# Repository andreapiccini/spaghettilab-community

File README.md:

<p align="center">
  <a href="https://spaghetti-lab.my.canva.site/">Website</a> •
  <a href="https://spaghetti-lab.my.canva.site/join-newsletter">Newsletter</a>
</p>

# SpaghettiLAB Community

From prototype to product.

SpaghettiLAB Community is the open development platform for learning,
experimenting, and building modular embedded and IoT prototypes. It includes
reference hardware, firmware, local software, protocols, integrations, tests,
and examples without artificial feature restrictions.

A prototype is not automatically suitable for production. Professional
deployments also require qualified hardware, secure provisioning, verified
updates, release traceability, lifecycle maintenance, and accountable support.
Those production capabilities are developed and delivered separately so that
organizations can adopt SpaghettiLAB without weakening the open Community
platform.

## Repository structure

- `hardware/` — Core, Backbone, and Module reference designs.
- `firmware/` — Community firmware, SDKs, examples, and verification.
- `software/` — Local Studio, dashboard, Node-RED integration, and packages.
- `contracts/` — Public, language-neutral protocol contracts and golden fixtures.
- `examples/` — End-to-end example systems.
- `docs/` — Documentation licensing and notices.

The Community hardware tree intentionally contains editable KiCad sources, not
generated manufacturing packages. Official production files, factory tooling,
secure provisioning infrastructure, managed cloud services, and commercial
support are maintained separately.

## Open-core model

SpaghettiLAB follows an open-core hardware model with a clear boundary:

- **Community layer:** the source files actually published in this repository,
  licensed under the open-source and open-hardware licences listed below. These
  licences permit commercial use when their conditions are followed.
- **Production layer:** the separately maintained, release-specific package used
  for official commercial products and authorized manufacturing partners.

The Production layer is not part of this repository. It may include validated
Gerber and drill outputs, approved BOM and alternate-part data, pick-and-place
files, panelization and assembly profiles, test fixtures and procedures,
production firmware or provisioning material, enclosure and packaging files,
quality-control criteria, release traceability, and supplier-specific data.
Access to those materials, use of official SpaghettiLAB branding, and the right
to present a product as official or partner-produced require prior written
authorization under a separate commercial or manufacturing agreement.

Anyone may generate their own manufacturing outputs from the public hardware
sources and make or sell products as permitted by CERN-OHL-S-2.0. Such products
must comply with that licence and must not imply official manufacture,
certification, warranty, endorsement, or partnership. See
[`COMMERCIAL.md`](COMMERCIAL.md) and [`TRADEMARK.md`](TRADEMARK.md).

## Hardware projects

- `hardware/core/core.kicad_pro`
- `hardware/backbone/backbone.kicad_pro`
- `hardware/modules/nfc-tag/nfc-tag.kicad_pro`

The KiCad source files embed the symbols and footprints already used by each
design. Some optional 3D models reference the `SPAGHETTI_LIB` environment
variable and are not required to open the schematic or PCB.

## Community and production

The Community platform is intended for education, research, development,
prototyping, and open products. Organizations may evaluate and extend it under
the applicable open-source and open-hardware licenses.

SpaghettiLAB Production adds the controlled engineering work needed to turn a
prototype into a supported product: qualified hardware, secure device identity,
signed releases, manufacturing support, managed updates, fleet operations, and
long-term maintenance.

## Citation

If you use SpaghettiLAB in research, publications, articles, videos, educational
material, or derivative projects, please cite:

> Piccini, A. (2026).  
> SpaghettiLAB: Modular Stackable Electronics Platform.  
> GitHub Repository.  
> https://github.com/andreapiccini/SpaghettiLAB

A machine-readable citation file is available in `CITATION.cff`.

## Licensing

The current Community generation retains the licenses already applied to its
components:

| Content | License |
|---|---|
| Firmware | GPL-3.0-or-later |
| Public applications and services | AGPL-3.0-or-later |
| Protocols and selected integration SDKs | Apache License 2.0 |
| Hardware reference designs | CERN-OHL-S-2.0 |
| Documentation | CC BY 4.0 |

See [`LICENSES.md`](LICENSES.md) for the exact repository map,
[`CONTRIBUTING.md`](CONTRIBUTING.md) for DCO contribution requirements, and
[`TRADEMARK.md`](TRADEMARK.md) for product identity rules. The copyleft transition
does not alter rights granted for earlier versions.

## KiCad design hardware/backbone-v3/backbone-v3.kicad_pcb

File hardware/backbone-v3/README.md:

# Backbone V3

Aprire `backbone-v3.kicad_pro` in KiCad. Il progetto contiene lo schema gerarchico e il PCB da **68,5 × 63,5 mm**. L’[anteprima interattiva](anteprima-interattiva.html) simula i quattro comandi, Play/Stop, il blocco e le quattro memorie. Le modalità delle righe sono 3.3V, GND, MCU e X (scollegata). I tasti in basso hanno solo le icone.

## Touch

Un Holtek BS8112A-3 (LCSC C91296), alimentato a 3,3 V con C944 da 100 nF, legge i quattro elettrodi anulari sotto la solder mask. Usa il bus I²C interno esistente, con indirizzo a 7 bit `0x50`. L’ESP32-S3 e l’ESP32-S31 condividono la stessa interfaccia. Gli ingressi inutilizzati e KEY12/IRQ restano aperti.

| Ingresso | Bit di KeyStatus0 | Comando |
| --- | --- | --- |
| KEY1 | 0 | Play/Stop |
| KEY2 | 1 | + |
| KEY3 | 2 | Mode |
| KEY4 | 3 | Load/Save |

Il firmware deve leggere `KeyStatus0` (`0x08`) in polling, interpretando 1 come tasto premuto. L’I²C va configurato a non più di 100 kbit/s con supporto al clock stretching e timeout. Le soglie dei quattro canali si impostano in software all’avvio entro la finestra indicata nel datasheet. Il comportamento dei comandi è simulato nell’anteprima. I tre segmenti della batteria sono indipendenti e attendono il dato di carica dal modulo batteria.

## Frontale e LED

Il driver IS31FL3731 (I²C interno, 0x74) pilota 105 LED. La [mappa del frontale](layout.json) riporta le reti di anodo e catodo, il registro PWM e il codice LCSC per ciascun emettitore. Le 16 righe hanno 64 LED 0402 a ±45°. I 0603 sono stati usati dove le piazzole rispettano le aperture e lo spazio disponibile. In totale ci sono 86 LED 0402 e 19 LED 0603. Il logo usa 20 LED blu (16 da 0402 e 4 da 0603) distribuiti su simbolo e lettere.

Le finestre sono aperture nelle due solder mask con esclusione di rame sui quattro strati. Rimane FR-4 pieno. I LED sono componenti a emissione frontale, piazzati sul Top per la prova di montaggio rivolto verso il laminato. Servono un campione per verificare saldabilità, uniformità della luce e sensibilità degli elettrodi, e il routing del PCB prima della fabbricazione. J32 e J33 sono stati riposizionati per liberare le finestre.

## Verifica KiCad

Lo schema ha superato l’ERC senza errori. Sono state confrontate 1.049 associazioni piazzola–rete tra schema e PCB. Il DRC non segnala cortocircuiti o piazzole nelle aree ottiche. Restano 499 connessioni da instradare e segnalazioni su courtyard, serigrafia e distanze del PCB, comprese quelle dei contatti magnetici al bordo.

## Variante RGB

L’[anteprima RGB con MODE](anteprima-rgb-mode.html) conserva il confronto con la proposta precedente.

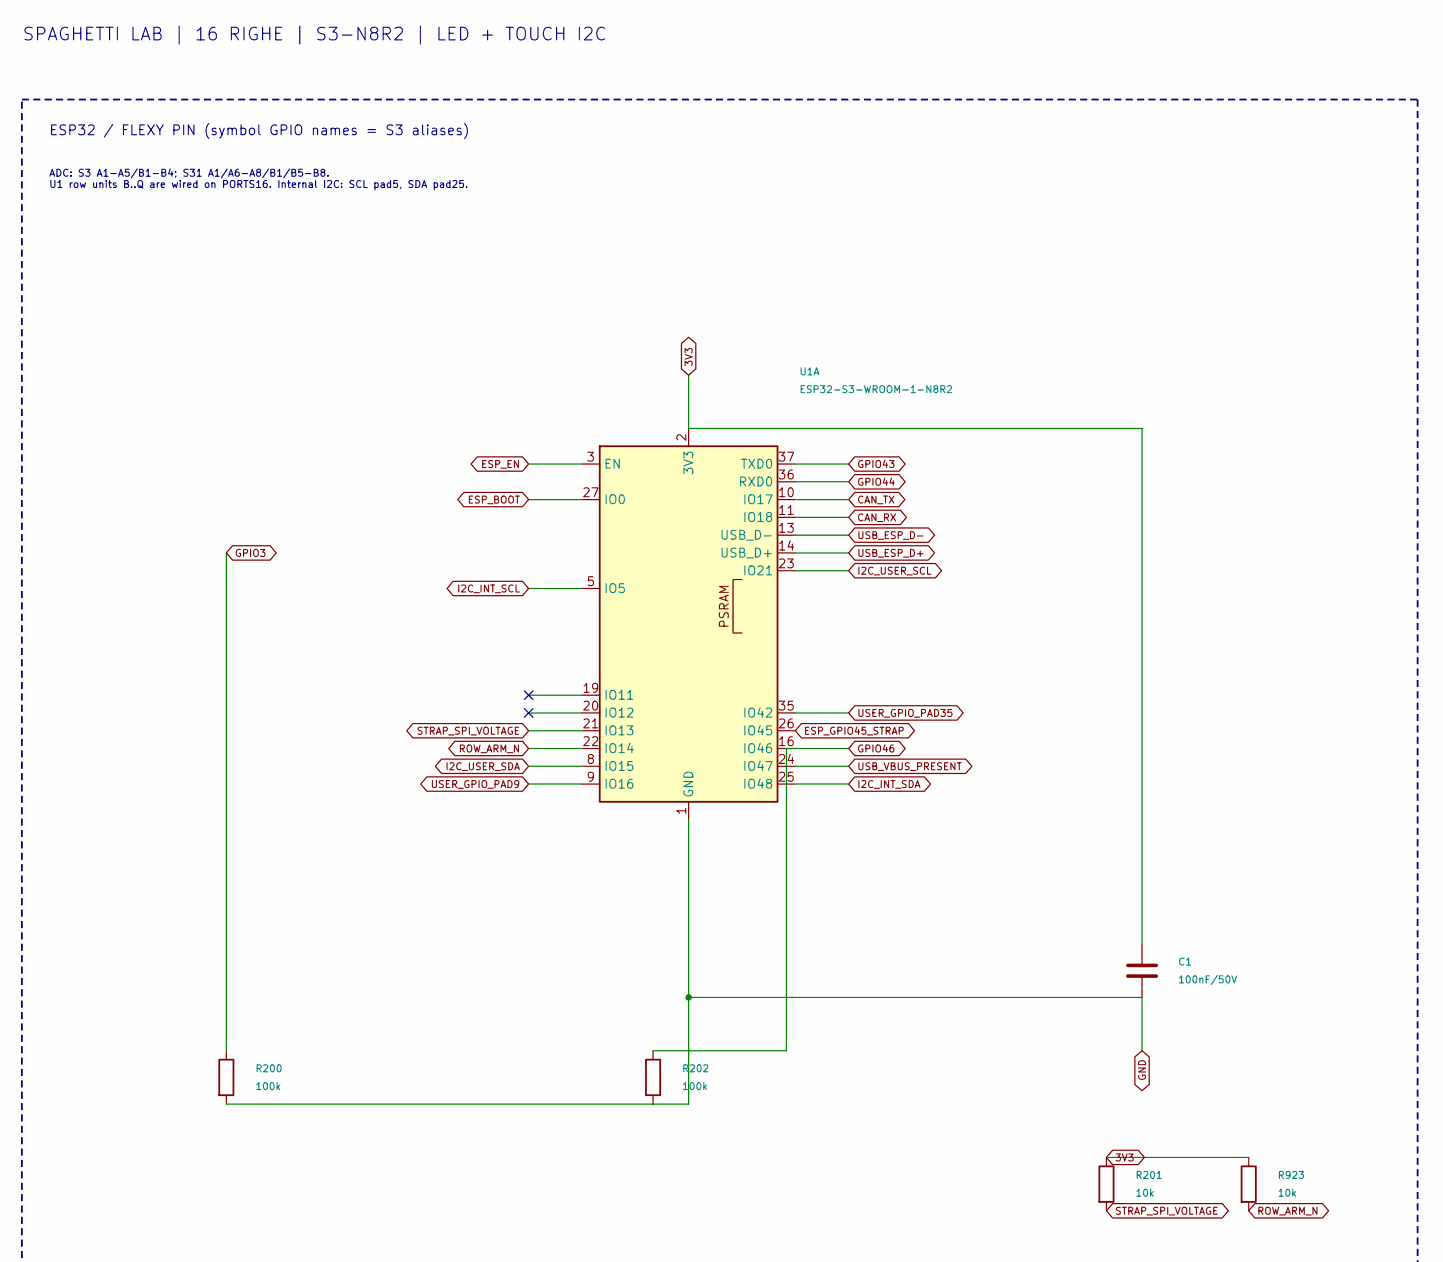
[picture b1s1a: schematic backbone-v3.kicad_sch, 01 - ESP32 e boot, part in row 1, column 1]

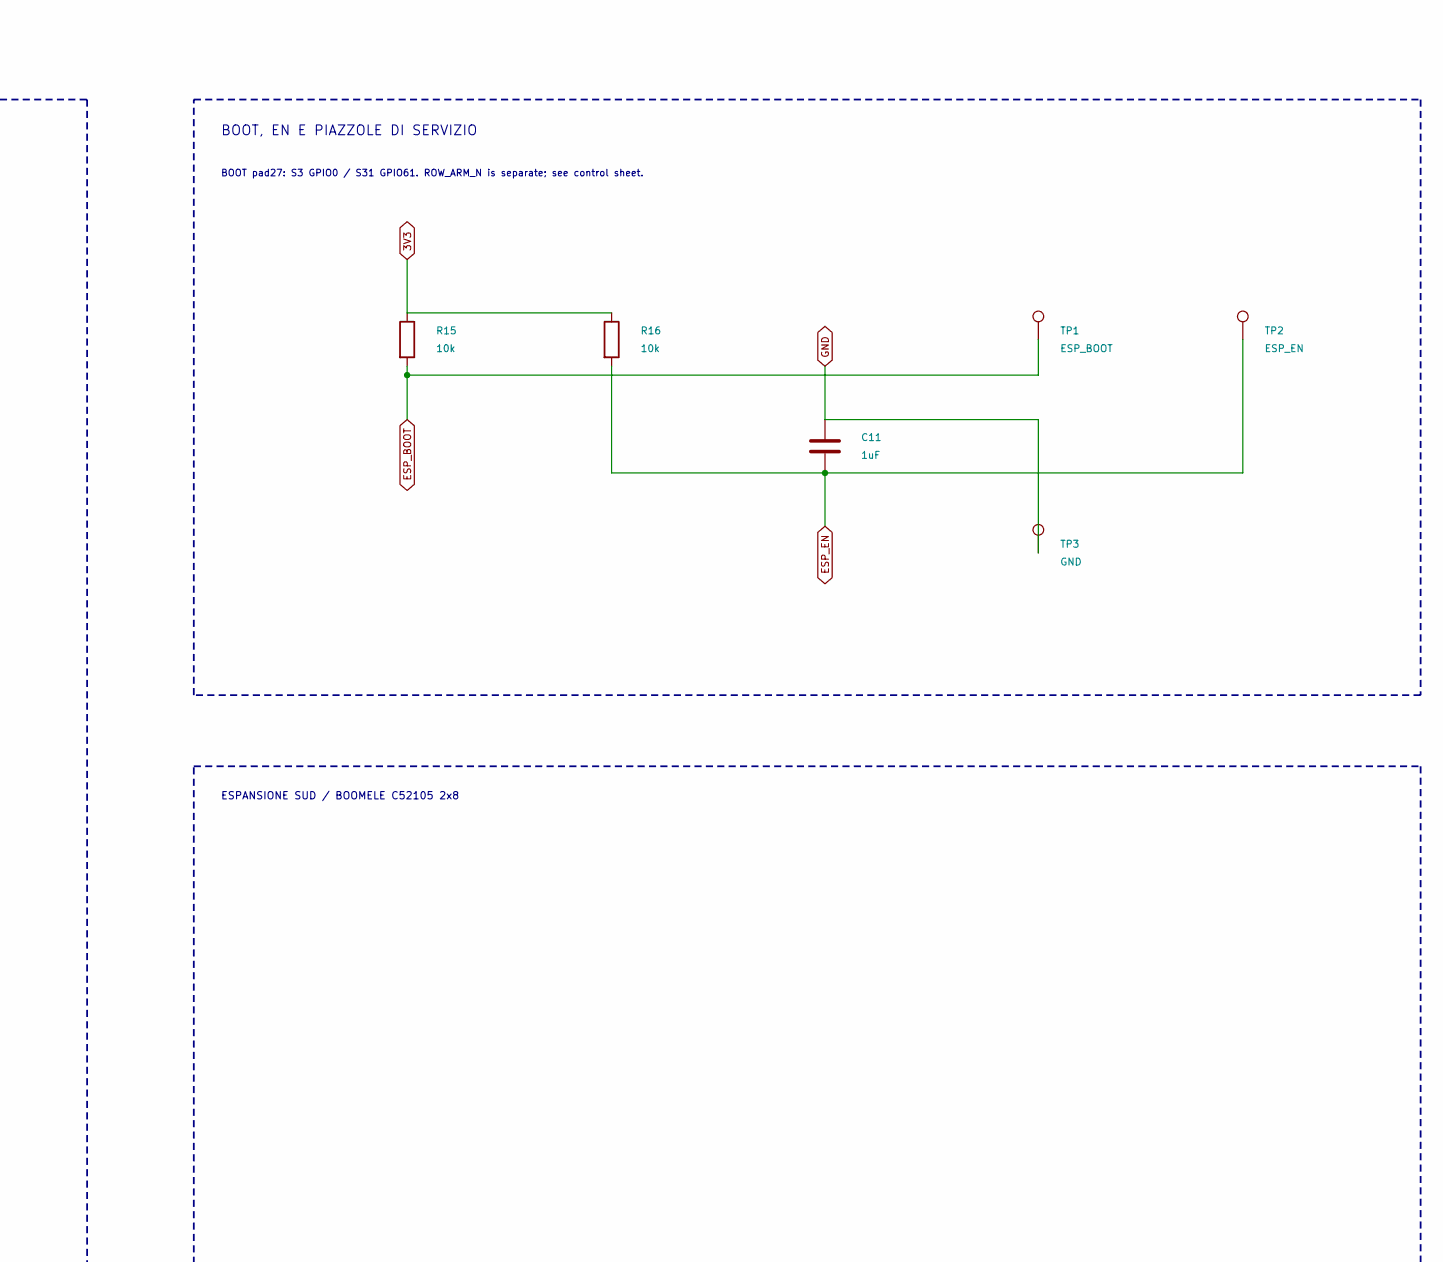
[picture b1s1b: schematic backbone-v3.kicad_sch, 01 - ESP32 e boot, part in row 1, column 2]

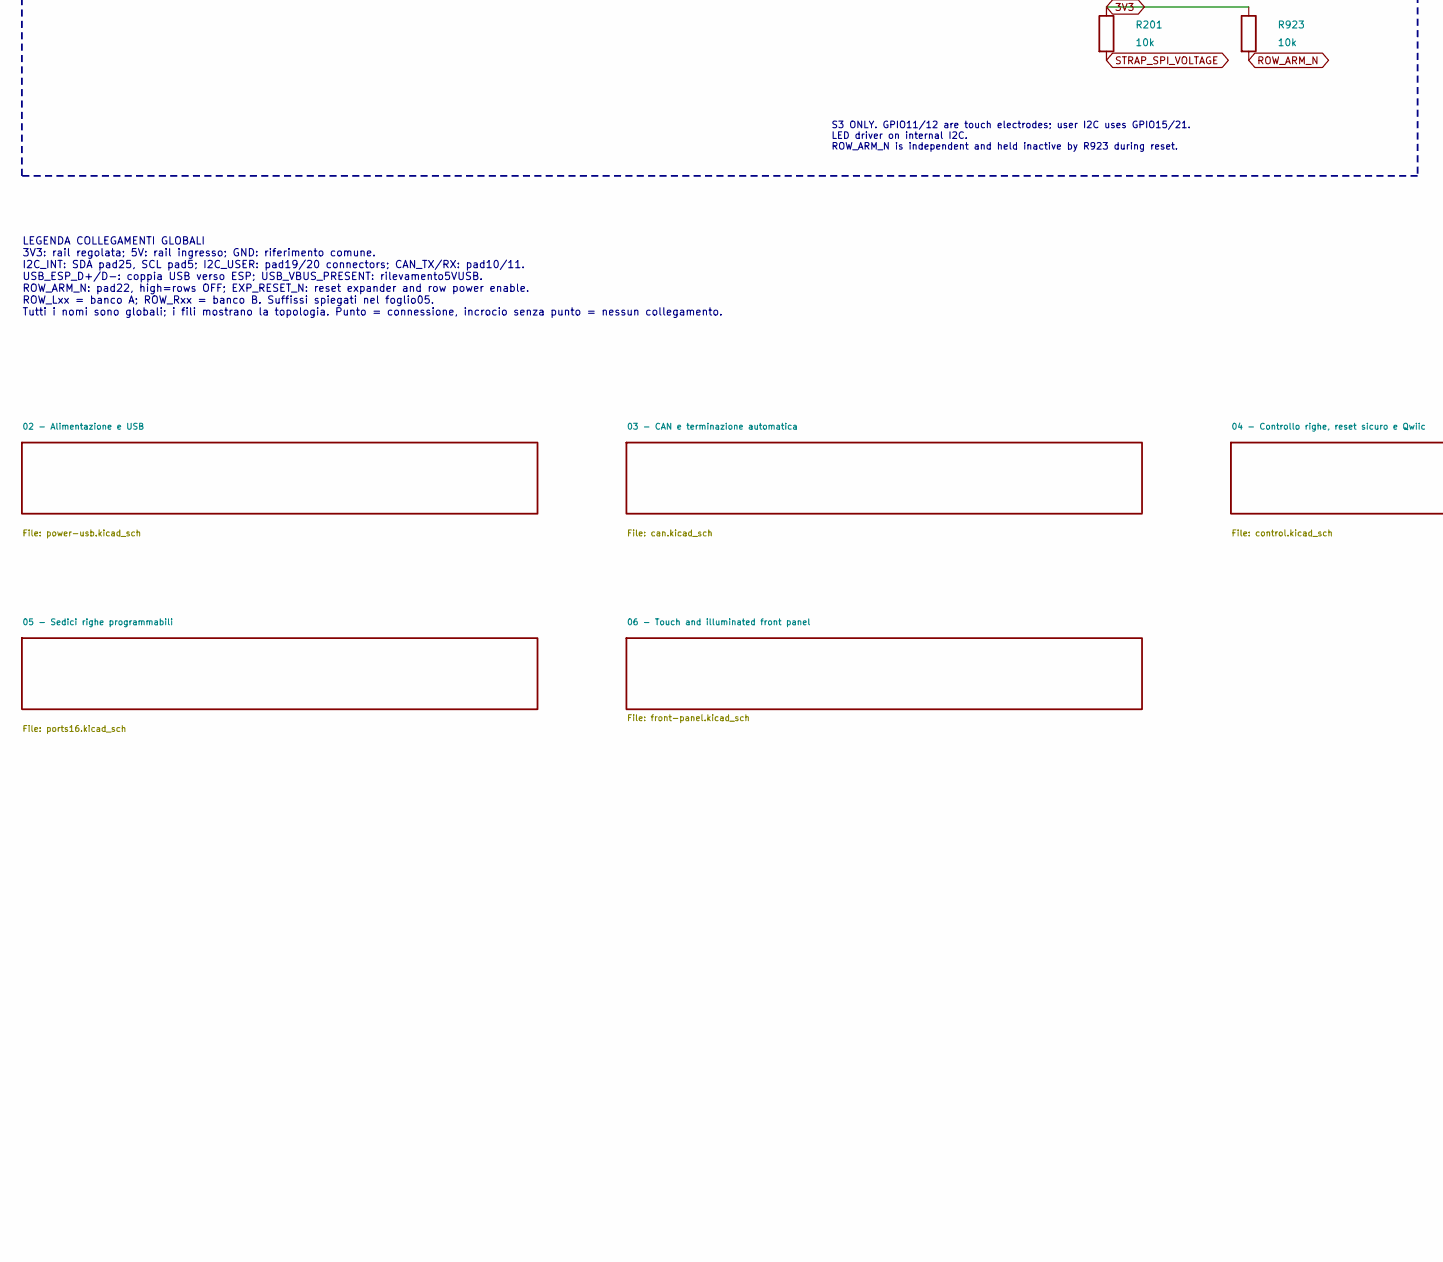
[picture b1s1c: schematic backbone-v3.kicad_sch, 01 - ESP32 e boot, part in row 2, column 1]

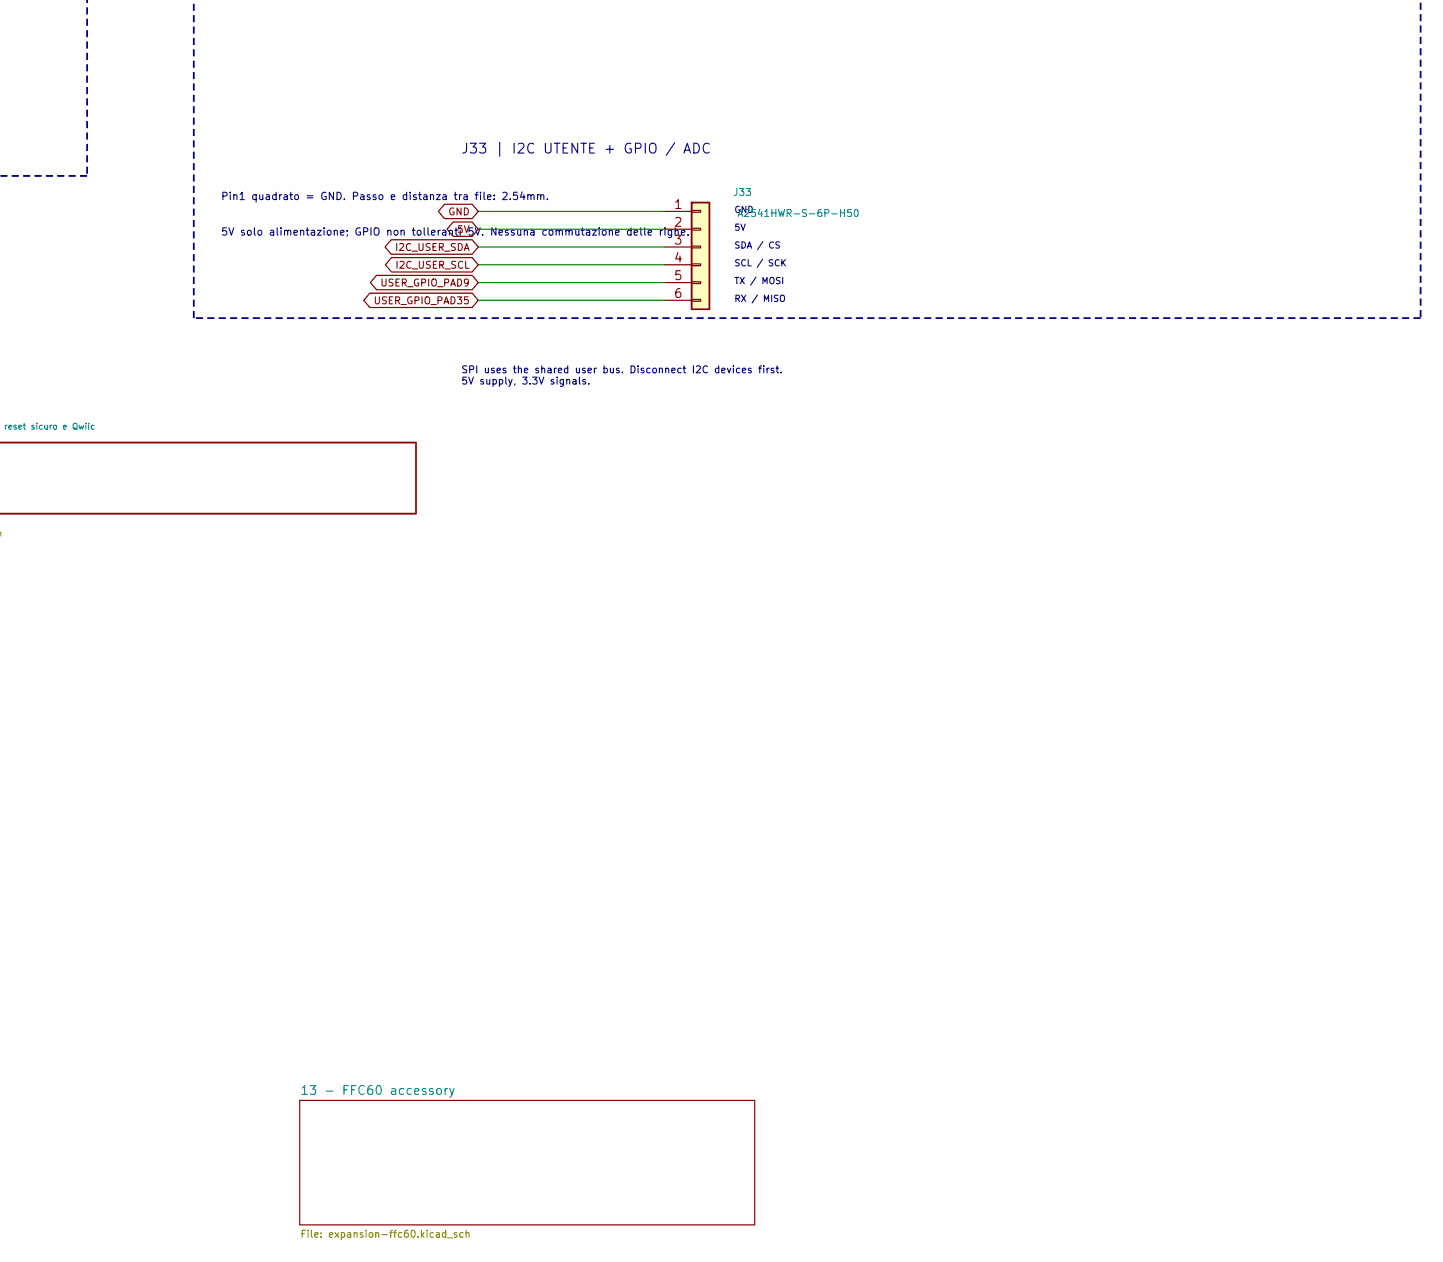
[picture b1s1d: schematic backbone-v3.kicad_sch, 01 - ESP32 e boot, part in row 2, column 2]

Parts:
C1: 100nF/50V; C0603; MPN CL10B104KB8NNNC; LCSC Part Name C1591
C11: 1uF; C0603; LCSC Part Name C128624
J33: A2541HWR-S-6P-H50; CJT_A2541HWR-S-6P-H50
R15, R16: 10k; R0603; MPN 0603WAF1002T5E; LCSC Part C25804
R200, R202: 100k; R_0603_1608Metric
R201: 10k; R_0603_1608Metric
R923: 10k; R_0603_1608Metric; MPN 0603WAF1002T5E; LCSC Part C25804
TP1: ESP_BOOT; TestPoint_Pad_D1.5mm
TP2: ESP_EN; TestPoint_Pad_D1.5mm
TP3: GND; TestPoint_Pad_D1.5mm
U1: ESP32-S3-WROOM-1-N8R2; ESP32-S3-WROOM-1_FlexyPin_N8R2_TwoSideCourtyard; MPN ESP32-S3-WROOM-1-N8R2

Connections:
3V3: C1.1, R15.1, R16.1, R201.1, R923.1, U1.2 (3V3); also elsewhere on the board
CAN_RX: U1.11 (IO18); also elsewhere on the board
CAN_TX: U1.10 (IO17); also elsewhere on the board
ESP_BOOT: R15.2, TP1.1, U1.27 (IO0)
ESP_EN: C11.2, R16.2, TP2.1, U1.3 (EN); also elsewhere on the board
ESP_GPIO45_STRAP: U1.26 (IO45); also elsewhere on the board
GND: C1.2, C11.1, J33.1, R200.2, R202.2, TP3.1, U1.1 (GND), U1.40 (GND); also elsewhere on the board
GPIO3: R200.1; also elsewhere on the board
GPIO43: U1.37 (TXD0); also elsewhere on the board
GPIO44: U1.36 (RXD0); also elsewhere on the board
GPIO46: R202.1, U1.16 (IO46)
I2C_INT_SCL: U1.5 (IO5); also elsewhere on the board
I2C_INT_SDA: U1.25 (IO48); also elsewhere on the board
I2C_USER_SCL: J33.4, U1.23 (IO21); also elsewhere on the board
I2C_USER_SDA: J33.3, U1.8 (IO15); also elsewhere on the board
ROW_ARM_N: R923.2, U1.22 (IO14); also elsewhere on the board
STRAP_SPI_VOLTAGE: R201.2, U1.21 (IO13)
USB_ESP_D+: U1.14 (USB_D+); also elsewhere on the board
USB_ESP_D-: U1.13 (USB_D-); also elsewhere on the board
USB_VBUS_PRESENT: U1.24 (IO47); also elsewhere on the board
USER_GPIO_PAD9: J33.5, U1.9 (IO16); also elsewhere on the board
USER_GPIO_PAD35: J33.6, U1.35 (IO42); also elsewhere on the board

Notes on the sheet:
TX / MOSI
LEGENDA COLLEGAMENTI GLOBALI 3V3: rail regolata; 5V: rail ingresso; GND: riferimento comune. I2C_INT: SDA pad25, SCL pad5; I2C_USER: pad19/20 connectors; CAN_TX/RX: pad10/11. USB_ESP_D+/D-: coppia USB verso ESP; USB_VBUS_PRESENT: rilevamento5VUSB. ROW_ARM_N: pad22, high=rows OFF; EXP_RESET_N: reset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
SPI uses the shared user bus. Disconnect I2C devices first. 5V supply, 3.3V signals.
GND
SPAGHETTI LAB | 16 RIGHE | S3-N8R2 | LED + TOUCH I2C
ESP32 / FLEXY PIN (symbol GPIO names = S3 aliases)
J33 | I2C UTENTE + GPIO / ADC
BOOT, EN E PIAZZOLE DI SERVIZIO
S3 ONLY. GPIO11/12 are touch electrodes; user I2C uses GPIO15/21. LED driver on internal I2C. ROW_ARM_N is independent and held inactive by R923 during reset.
SCL / SCK
5V solo alimentazione; GPIO non tolleranti 5V. Nessuna commutazione delle righe.
ESPANSIONE SUD / BOOMELE C52105 2x8
SDA / CS
RX / MISO
ADC: S3 A1-A5/B1-B4; S31 A1/A6-A8/B1/B5-B8. U1 row units B..Q are wired on PORTS16. Internal I2C: SCL pad5, SDA pad25.
Pin1 quadrato = GND. Passo e distanza tra file: 2.54mm.
BOOT pad27: S3 GPIO0 / S31 GPIO61. ROW_ARM_N is separate; see control sheet.

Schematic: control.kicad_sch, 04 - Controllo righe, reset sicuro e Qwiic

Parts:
C200, C204, C205, C206: 100nF; C_0603_1608Metric
J4: SM04B-SRSS-TB(LF)(SN); JST_SH_SM04B-SRSS-TB_1x04-1MP_P1.00mm_Horizontal; MPN SM04B-SRSS-TB(LF)(SN); LCSC C160404
R24, R25: 4.7k; R0603
R203: 10k; R_0603_1608Metric
R302, R303: 4.7k; R_0603_1608Metric; MPN 0603WAF4701T5E; LCSC Part C23162
U40, U41, U42: FCA9539Q; FCA9539Q_WQFN24_4x4; MPN FCA9539Q; LCSC Part C55318342
U60: SN74LVC1G97DBVR; SOT-23-6; MPN SN74LVC1G97DBVR; LCSC Part C128411

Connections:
3V3: C200.1, C204.1, C205.1, C206.1, J4.2 (+3V3), R24.1, R25.1, R302.1, R303.1, U40.18 (A0), U40.21 (VCC), U41.21 (VCC), U41.23 (A1), U42.18 (A0), U42.21 (VCC), U42.23 (A1), U60.5 (VCC); also elsewhere on the board
ESP_EN: U60.1 (IN1_/_EN); also elsewhere on the board
EXP_RESET_N: R203.1, U40.24 (RESET_N), U41.24 (RESET_N), U42.24 (RESET_N), U60.4 (Y); also elsewhere on the board
GND: C200.2, C204.2, C205.2, C206.2, J4.1 (GND), R203.2, U40.9 (GND), U40.23 (A1), U40.25 (EP_/_GND), U41.9 (GND), U41.18 (A0), U41.25 (EP_/_GND), U42.9 (GND), U42.25 (EP_/_GND), U60.2 (GND), U60.3 (IN0_=_0); also elsewhere on the board
I2C_INT_SCL: R303.2, U40.19 (SCL), U41.19 (SCL), U42.19 (SCL); also elsewhere on the board
I2C_INT_SDA: R302.2, U40.20 (SDA), U41.20 (SDA), U42.20 (SDA); also elsewhere on the board
I2C_USER_SCL: J4.4 (SCL), R25.2; also elsewhere on the board
I2C_USER_SDA: J4.3 (SDA), R24.2; also elsewhere on the board
ROW_ARM_N: U60.6 (IN2_/_ARM_N); also elsewhere on the board
ROW_L01_ISO_N: U42.1 (P0.0); also elsewhere on the board
ROW_L01_NG: U40.2 (P0.1); also elsewhere on the board
ROW_L01_PG: U40.1 (P0.0); also elsewhere on the board
ROW_L02_ISO_N: U42.2 (P0.1); also elsewhere on the board
ROW_L02_NG: U40.4 (P0.3); also elsewhere on the board
ROW_L02_PG: U40.3 (P0.2); also elsewhere on the board
ROW_L03_ISO_N: U42.3 (P0.2); also elsewhere on the board
ROW_L03_NG: U40.6 (P0.5); also elsewhere on the board
ROW_L03_PG: U40.5 (P0.4); also elsewhere on the board
ROW_L04_ISO_N: U42.4 (P0.3); also elsewhere on the board
ROW_L04_NG: U40.8 (P0.7); also elsewhere on the board
ROW_L04_PG: U40.7 (P0.6); also elsewhere on the board
ROW_L05_ISO_N: U42.5 (P0.4); also elsewhere on the board
ROW_L05_NG: U40.11 (P1.1); also elsewhere on the board
ROW_L05_PG: U40.10 (P1.0); also elsewhere on the board
ROW_L06_ISO_N: U42.6 (P0.5); also elsewhere on the board
ROW_L06_NG: U40.13 (P1.3); also elsewhere on the board
ROW_L06_PG: U40.12 (P1.2); also elsewhere on the board
ROW_L07_ISO_N: U42.7 (P0.6); also elsewhere on the board
ROW_L07_NG: U40.15 (P1.5); also elsewhere on the board
ROW_L07_PG: U40.14 (P1.4); also elsewhere on the board
ROW_L08_ISO_N: U42.8 (P0.7); also elsewhere on the board
ROW_L08_NG: U40.17 (P1.7); also elsewhere on the board
ROW_L08_PG: U40.16 (P1.6); also elsewhere on the board
ROW_R01_ISO_N: U42.10 (P1.0); also elsewhere on the board
ROW_R01_NG: U41.2 (P0.1); also elsewhere on the board
ROW_R01_PG: U41.1 (P0.0); also elsewhere on the board
ROW_R02_ISO_N: U42.11 (P1.1); also elsewhere on the board
ROW_R02_NG: U41.4 (P0.3); also elsewhere on the board
ROW_R02_PG: U41.3 (P0.2); also elsewhere on the board
ROW_R03_ISO_N: U42.12 (P1.2); also elsewhere on the board
ROW_R03_NG: U41.6 (P0.5); also elsewhere on the board
ROW_R03_PG: U41.5 (P0.4); also elsewhere on the board
ROW_R04_ISO_N: U42.13 (P1.3); also elsewhere on the board
ROW_R04_NG: U41.8 (P0.7); also elsewhere on the board
ROW_R04_PG: U41.7 (P0.6); also elsewhere on the board
ROW_R05_ISO_N: U42.14 (P1.4); also elsewhere on the board
ROW_R05_NG: U41.11 (P1.1); also elsewhere on the board
ROW_R05_PG: U41.10 (P1.0); also elsewhere on the board
ROW_R06_ISO_N: U42.15 (P1.5); also elsewhere on the board
ROW_R06_NG: U41.13 (P1.3); also elsewhere on the board
ROW_R06_PG: U41.12 (P1.2); also elsewhere on the board
ROW_R07_ISO_N: U42.16 (P1.6); also elsewhere on the board
ROW_R07_NG: U41.15 (P1.5); also elsewhere on the board
ROW_R07_PG: U41.14 (P1.4); also elsewhere on the board
ROW_R08_ISO_N: U42.17 (P1.7); also elsewhere on the board
ROW_R08_NG: U41.17 (P1.7); also elsewhere on the board
ROW_R08_PG: U41.16 (P1.6); also elsewhere on the board

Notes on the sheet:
BUS INTERNO DEDICATO / GPIO4 SDA / GPIO5 SCL
BUS UTENTE GPIO11/12 / QWIIC / PULL-UP
PG/NG banco A: comandi di alimentazione. SCL/SDA: I2C; A0/A1: indirizzo; INT_N non usato.
EXP_RESET_N = ESP_EN AND NOT ROW_ARM_N. IN0 aGND. R203 mantiene reset basso se non pilotato; C200 bypass100nF.
U40 | FCA9539Q | 0x75
CONTROLLO48SEGNALI / RESET SICURO / I2C
INTERFACCIA LOCALE | DUE PULSANTI XKB
ISO_N A/B: isolamento GPIO, attivo basso. SCL/SDA: I2C; A0/A1: indirizzo; INT_N non usato.
U41 | FCA9539Q | 0x76
U42 | FCA9539Q | 0x77
INTERBLOCCO RESET / UNA SOLA PORTA
I2C_USER indipendente dai3expander: SDA GPIO11 / SCL GPIO12. Pull-up4,7k a3V3. 3V3/GND: alimentazione del moduloQwiic.
R302/R303: pull-up4,7k del solo bus interno. R24/R25: pull-up4,7k del bus utente, nel blocco Qwiic. Nessun collegamento SDA/SCL tra i due bus. Entrambi usano livelli3,3V; firmware: due controller distinti.
PG/NG banco B: comandi di alimentazione. SCL/SDA: I2C; A0/A1: indirizzo; INT_N non usato.
